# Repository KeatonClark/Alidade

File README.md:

# Alidade
A split wireless, ergo mechanical keyboard based on the switch layout of the [Corne V4](https://github.com/foostan/crkbd) by *foostan*.

View the documentation [here](https://KeatonClark.github.io/alidade)

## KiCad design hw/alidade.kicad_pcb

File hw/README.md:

# Alidade Hardware

Attribution to foostan for the board outline, switch placement, and various footprints and 3D models

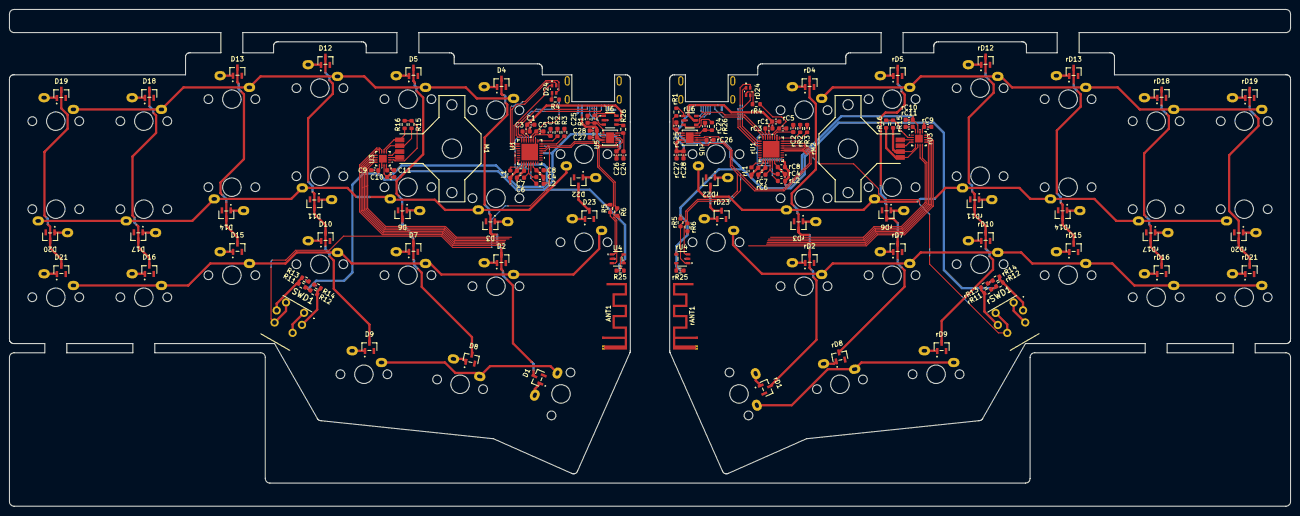
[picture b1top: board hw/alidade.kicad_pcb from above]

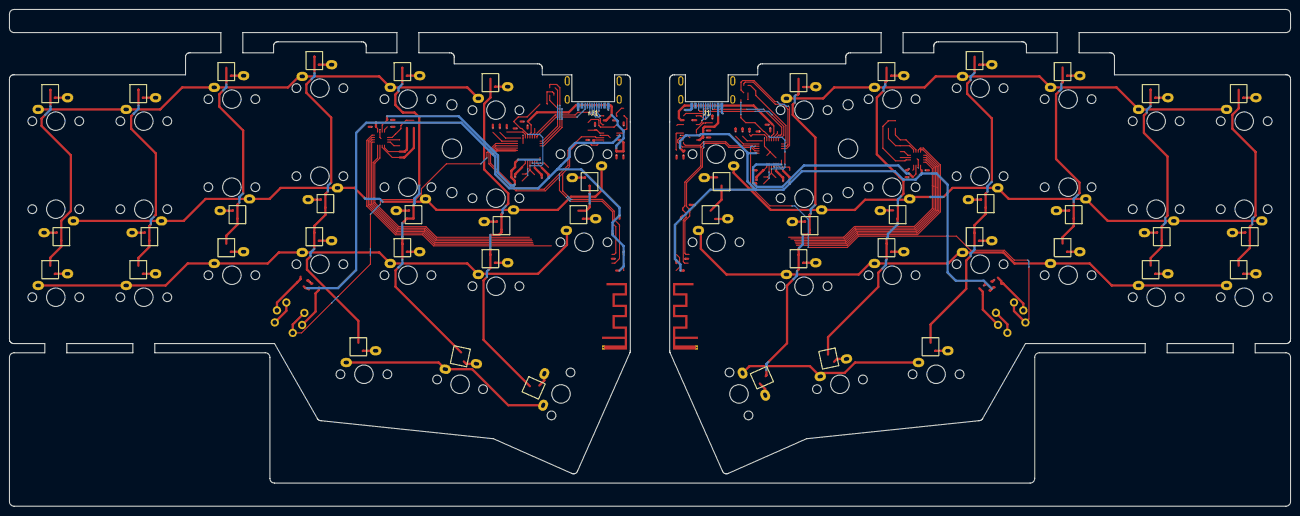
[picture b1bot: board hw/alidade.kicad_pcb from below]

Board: 4 copper layers, 277.2 x 107.5 mm, 176 parts (48 on the bottom side), 138 nets.

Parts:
ANT1: SWRA117D; Texas_SWRA117D_2.4GHz_Left
C1, C3: 1u; C_0603_1608Metric
C2: 2.2u; C_0603_1608Metric
C4, C5, C6, C7, C8: 10u; C_0603_1608Metric
C9, C10, C11, C26, C28: 100n; C_0603_1608Metric
C24, C25: 47p; C_0603_1608Metric
C27: 4.7u; C_0603_1608Metric
D1, D2, D3, D4, D5, D6, D7, D8, D9, D10, D11, D12, D13, D14, D15, D16, D17, D18, D19, D20, D21, D22, D23: BAT54; SOT23
D24: 19-237/R6GHBHC-A01/2T; 19-237_R6GHBHC-A01_2T
EXSW1, EXSW2: SW_Push; CherryMX_1u
J1: TYPE-C-31-M-13C
L1, L2: 2.2u; L_0603_1608Metric
M1: SK8701-01-005-SENSOR; SK8707-01-005-SENSOR
R1, R26: 27; R_0603_1608Metric
R2: 47k; R_0603_1608Metric
R3, R4, R13, R14: 0; R_0603_1608Metric
R5, R6, R11, R12, R25: 10k; R_0603_1608Metric
R15, R16: 2.4k; R_0603_1608Metric
SW1, SW2, SW3, SW4, SW5, SW6, SW7, SW8, SW9, SW10, SW11, SW12, SW13, SW14, SW15, SW16, SW17, SW18, SW19, SW20, SW21: SW_Push; CherryMX_1u
SWD1: 228ADS2AAWFCMBA; 228ADS2
U1: NPM1300-QEAA-R; QFN32_5X5
U3: ADS122S14IRTER; WQFN16_3X3
U4: AT24C32E-STUM-T; TSOT5_MC_MCH
U5: FT200XD; DFN-10_FTD
U6: USBLC6-2SC6; SOT23-6L_STM
rANT1: SWRA117D; Texas_SWRA117D_2.4GHz_Right
rC1, rC3: 1u; C_0603_1608Metric
rC2: 2.2u; C_0603_1608Metric
rC4, rC5, rC6, rC7, rC8: 10u; C_0603_1608Metric
rC9, rC10, rC11, rC26, rC28: 100n; C_0603_1608Metric
rC24, rC25: 47p; C_0603_1608Metric
rC27: 4.7u; C_0603_1608Metric
rD1, rD2, rD3, rD4, rD5, rD6, rD7, rD8, rD9, rD10, rD11, rD12, rD13, rD14, rD15, rD16, rD17, rD18, rD19, rD20, rD21, rD22, rD23: BAT54; SOT23
rD24: 19-237/R6GHBHC-A01/2T; 19-237_R6GHBHC-A01_2T
rEXSW1, rEXSW2: SW_Push; CherryMX_1u
rJ1: TYPE-C-31-M-13C
rL1, rL2: 2.2u; L_0603_1608Metric
rM2: SK8701-01-005-SENSOR; SK8707-01-005-SENSOR
rR1, rR26: 27; R_0603_1608Metric
rR2: 47k; R_0603_1608Metric
rR3, rR4, rR13, rR14: 0; R_0603_1608Metric
rR5, rR6, rR11, rR12, rR25: 10k; R_0603_1608Metric
rR15, rR16: 2.4k; R_0603_1608Metric
rSW1, rSW2, rSW3, rSW4, rSW5, rSW6, rSW7, rSW8, rSW9, rSW10, rSW11, rSW12, rSW13, rSW14, rSW15, rSW16, rSW17, rSW18, rSW19, rSW20, rSW21: SW_Push; CherryMX_1u
rSWD1: 228ADS2AAWFCMBA; 228ADS2
rU1: NPM1300-QEAA-R; QFN32_5X5
rU3: ADS122S14IRTER; WQFN16_3X3
rU4: AT24C32E-STUM-T; TSOT5_MC_MCH
rU5: FT200XD; DFN-10_FTD
rU6: USBLC6-2SC6; SOT23-6L_STM

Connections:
/HID/AIN0: M1.B, U3.4 (AIN3)
/HID/AIN1: M1.A, U3.3 (AIN2)
/HID/COL1: D22.3 (K), D23.3 (K)
/HID/COL2: D1.3 (K), D2.3 (K), D3.3 (K), D4.3 (K)
/HID/COL3: D5.3 (K), D6.3 (K), D7.3 (K), D8.3 (K)
/HID/COL4: D9.3 (K), D10.3 (K), D11.3 (K), D12.3 (K)
/HID/COL5: D13.3 (K), D14.3 (K), D15.3 (K)
/HID/COL6: D16.3 (K), D17.3 (K), D18.3 (K)
/HID/COL7: D19.3 (K), D20.3 (K), D21.3 (K)
/HID/REFN: M1.D, R16.2, U3.6 (AIN5/REFN/GPIO1)
/HID/REFP: M1.C, R15.1, U3.5 (AIN4/REFP/GPIO0)
/HID/ROW1: SW4.1, SW5.1, SW12.1, SW13.1, SW18.1, SW19.1
/HID/ROW2: EXSW1.1, SW3.1, SW6.1, SW11.1, SW14.1, SW17.1, SW20.1
/HID/ROW3: EXSW2.1, SW2.1, SW7.1, SW10.1, SW15.1, SW16.1, SW21.1
/HID/ROW4: SW1.1, SW8.1, SW9.1
/HID/SHPHLD: SWD1.3, SWD1.4, U1.15 (SHPHLD)
/HID/rAIN0: rM2.B, rU3.4 (AIN3)
/HID/rAIN1: rM2.A, rU3.3 (AIN2)
/HID/rCOL1: rD22.3 (K), rD23.3 (K)
/HID/rCOL2: rD1.3 (K), rD2.3 (K), rD3.3 (K), rD4.3 (K)
/HID/rCOL3: rD5.3 (K), rD6.3 (K), rD7.3 (K), rD8.3 (K)
/HID/rCOL4: rD9.3 (K), rD10.3 (K), rD11.3 (K), rD12.3 (K)
/HID/rCOL5: rD13.3 (K), rD14.3 (K), rD15.3 (K)
/HID/rCOL6: rD16.3 (K), rD17.3 (K), rD18.3 (K)
/HID/rCOL7: rD19.3 (K), rD20.3 (K), rD21.3 (K)
/HID/rREFN: rM2.D, rR16.2, rU3.6 (AIN5/REFN/GPIO1)
/HID/rREFP: rM2.C, rR15.1, rU3.5 (AIN4/REFP/GPIO0)
/HID/rROW1: rSW4.1, rSW5.1, rSW12.1, rSW13.1, rSW18.1, rSW19.1
/HID/rROW2: rEXSW1.1, rSW3.1, rSW6.1, rSW11.1, rSW14.1, rSW17.1, rSW20.1
/HID/rROW3: rEXSW2.1, rSW2.1, rSW7.1, rSW10.1, rSW15.1, rSW16.1, rSW21.1
/HID/rROW4: rSW1.1, rSW8.1, rSW9.1
/HID/rSHPHLD: rSWD1.3, rSWD1.4, rU1.15 (SHPHLD)
/MCU/SCL: R5.2, U1.14 (SCL), U4.1 (SCL), U5.6 (SCL)
/MCU/SDA: R6.2, U1.13 (SDA), U4.3 (SDA), U5.8 (SDA)
/MCU/rSCL: rR5.2, rU1.14 (SCL), rU4.1 (SCL), rU5.6 (SCL)
/MCU/rSDA: rR6.2, rU1.13 (SDA), rU4.3 (SDA), rU5.8 (SDA)
/PMIC/VBUS: C1.2, C27.1, C28.1, J1.A4 (VBUS), J1.A9 (VBUS), J1.B4 (VBUS), J1.B9 (VBUS), U1.21 (VBUS), U5.4 (VCC), U6.5 (VBUS)
/PMIC/VSYS: C4.1, C5.1, C6.1, R4.2, U1.4 (PVDD), U1.20 (VSYS)
/PMIC/rVBUS: rC1.2, rC27.1, rC28.1, rJ1.A4 (VBUS), rJ1.A9 (VBUS), rJ1.B4 (VBUS), rJ1.B9 (VBUS), rU1.21 (VBUS), rU5.4 (VCC), rU6.5 (VBUS)
/PMIC/rVSYS: rC4.1, rC5.1, rC6.1, rR4.2, rU1.4 (PVDD), rU1.20 (VSYS)
AVDD: C8.1, C10.1, L2.1, U1.32 (VOUT2), U3.15 (AVDD)
DVDD: C7.1, C9.1, C26.1, L1.1, R5.1, R6.1, R11.1, R12.2, R25.1, U1.1 (VOUT1), U1.12 (VDDIO), U3.13 (DVDD), U4.4 (VCC), U5.2 (RESET#), U5.7 (VCCIO)
GND: ANT1.2 (GND), C1.1, C2.2, C3.2, C4.2, C5.2, C6.2, C7.2, C8.2, C9.2, C10.2, C11.2, C24.2, C25.2, C26.2, C27.2, C28.2, J1.A1 (GND), J1.A12 (GND), J1.B1 (GND), J1.B12 (GND), J1.S1 (SHIELD), R2.1, R3.1, R13.2, R14.1, SWD1.1, SWD1.2, U1.2 (PVSS1), U1.6 (PVSS2), U1.18 (NTC), U1.33 (AVSS), U3.14 (GND), U3.17 (TP), U4.2 (GND), U5.9 (GND), U5.11 (GND), U6.2 (GND)
unnamed: D1.1 (A), SW1.2
unnamed: D2.1 (A), SW2.2
unnamed: D3.1 (A), SW3.2
unnamed: D4.1 (A), SW4.2
unnamed: D5.1 (A), SW5.2
unnamed: D6.1 (A), SW6.2
unnamed: D7.1 (A), SW7.2
unnamed: D8.1 (A), SW8.2
unnamed: D9.1 (A), SW9.2
unnamed: D10.1 (A), SW10.2
unnamed: D11.1 (A), SW11.2
unnamed: D12.1 (A), SW12.2
unnamed: D13.1 (A), SW13.2
unnamed: D14.1 (A), SW14.2
unnamed: D15.1 (A), SW15.2
unnamed: D16.1 (A), SW16.2
unnamed: D17.1 (A), SW17.2
unnamed: D18.1 (A), SW18.2
unnamed: D19.1 (A), SW19.2
unnamed: D20.1 (A), SW20.2
unnamed: D21.1 (A), SW21.2
unnamed: D22.1 (A), EXSW1.2
unnamed: D23.1 (A), EXSW2.2
unnamed: D24.3 (B), U1.27 (LED2)
unnamed: D24.2 (G), U1.26 (LED1)
unnamed: D24.4, R4.1
unnamed: D24.1 (R), U1.25 (LED0)
unnamed: J1.A5 (CC1), U1.23 (CC1)
unnamed: J1.B5 (CC2), U1.24 (CC2)
unnamed: J1.A6 (D+), J1.B6 (D+), U6.3 (I/O2)
unnamed: J1.A7 (D-), J1.B7 (D-), U6.1 (I/O1)
unnamed: C2.1, U1.19 (VBAT)
unnamed: R1.1, U6.6 (I/O1)
unnamed: R11.2, R13.1, SWD1.L1
unnamed: R12.1, R14.2, SWD1.L2
unnamed: R26.1, U6.4 (I/O2)
unnamed: C3.1, U1.22 (VBUSOUT)
unnamed: L1.2, U1.3 (SW1)
unnamed: R2.2, U1.17 (VSET1)
unnamed: L2.2, U1.5 (SW2)
unnamed: R3.2, U1.16 (VSET2)
unnamed: R25.2, U4.5 (WP)
unnamed: R15.2, R16.1, U3.2 (AIN1)
unnamed: C11.1, U3.16 (REFOUT)
unnamed: C25.1, R1.2, U5.1 (USBDM)
unnamed: C24.1, R26.2, U5.10 (USBDP)
unnamed: rD1.1 (A), rSW1.2
unnamed: rD2.1 (A), rSW2.2
unnamed: rD3.1 (A), rSW3.2
unnamed: rD4.1 (A), rSW4.2
unnamed: rD5.1 (A), rSW5.2
unnamed: rD6.1 (A), rSW6.2
unnamed: rD7.1 (A), rSW7.2
unnamed: rD8.1 (A), rSW8.2
unnamed: rD9.1 (A), rSW9.2
unnamed: rD10.1 (A), rSW10.2
unnamed: rD11.1 (A), rSW11.2
unnamed: rD12.1 (A), rSW12.2
unnamed: rD13.1 (A), rSW13.2
unnamed: rD14.1 (A), rSW14.2
unnamed: rD15.1 (A), rSW15.2
unnamed: rD16.1 (A), rSW16.2
unnamed: rD17.1 (A), rSW17.2
unnamed: rD18.1 (A), rSW18.2
unnamed: rD19.1 (A), rSW19.2
unnamed: rD20.1 (A), rSW20.2
unnamed: rD21.1 (A), rSW21.2
unnamed: rD22.1 (A), rEXSW1.2
unnamed: rD23.1 (A), rEXSW2.2
unnamed: rD24.3 (B), rU1.27 (LED2)
unnamed: rD24.2 (G), rU1.26 (LED1)
unnamed: rD24.4, rR4.1
unnamed: rD24.1 (R), rU1.25 (LED0)
unnamed: rJ1.A5 (CC1), rU1.23 (CC1)
unnamed: rJ1.B5 (CC2), rU1.24 (CC2)
unnamed: rJ1.A6 (D+), rJ1.B6 (D+), rU6.4 (I/O2)
unnamed: rJ1.A7 (D-), rJ1.B7 (D-), rU6.6 (I/O1)
unnamed: rC2.1, rU1.19 (VBAT)
unnamed: rR1.1, rU6.1 (I/O1)
unnamed: rR11.2, rR13.1, rSWD1.L1
unnamed: rR12.2, rR14.1, rSWD1.L2
unnamed: rR26.1, rU6.3 (I/O2)
unnamed: rC3.1, rU1.22 (VBUSOUT)
unnamed: rL1.2, rU1.3 (SW1)
unnamed: rR2.2, rU1.17 (VSET1)
unnamed: rL2.2, rU1.5 (SW2)
unnamed: rR3.2, rU1.16 (VSET2)
unnamed: rR25.2, rU4.5 (WP)
unnamed: rR15.2, rR16.1, rU3.2 (AIN1)
unnamed: rC11.1, rU3.16 (REFOUT)
unnamed: rC25.1, rR1.2, rU5.1 (USBDM)
unnamed: rC24.1, rR26.2, rU5.10 (USBDP)
rAVDD: rC8.1, rC10.1, rL2.1, rU1.32 (VOUT2), rU3.15 (AVDD)
rDVDD: rC7.1, rC9.1, rC26.1, rL1.1, rR5.1, rR6.1, rR11.1, rR12.1, rR25.1, rU1.1 (VOUT1), rU1.12 (VDDIO), rU3.13 (DVDD), rU4.4 (VCC), rU5.2 (RESET#), rU5.7 (VCCIO)
rGND: rANT1.2 (GND), rC1.1, rC2.2, rC3.2, rC4.2, rC5.2, rC6.2, rC7.2, rC8.2, rC9.2, rC10.2, rC11.2, rC24.2, rC25.2, rC26.2, rC27.2, rC28.2, rJ1.A1 (GND), rJ1.A12 (GND), rJ1.B1 (GND), rJ1.B12 (GND), rJ1.S1 (SHIELD), rR2.1, rR3.1, rR13.2, rR14.2, rSWD1.1, rSWD1.2, rU1.2 (PVSS1), rU1.6 (PVSS2), rU1.18 (NTC), rU1.33 (AVSS), rU3.14 (GND), rU3.17 (TP), rU4.2 (GND), rU5.9 (GND), rU5.11 (GND), rU6.2 (GND)

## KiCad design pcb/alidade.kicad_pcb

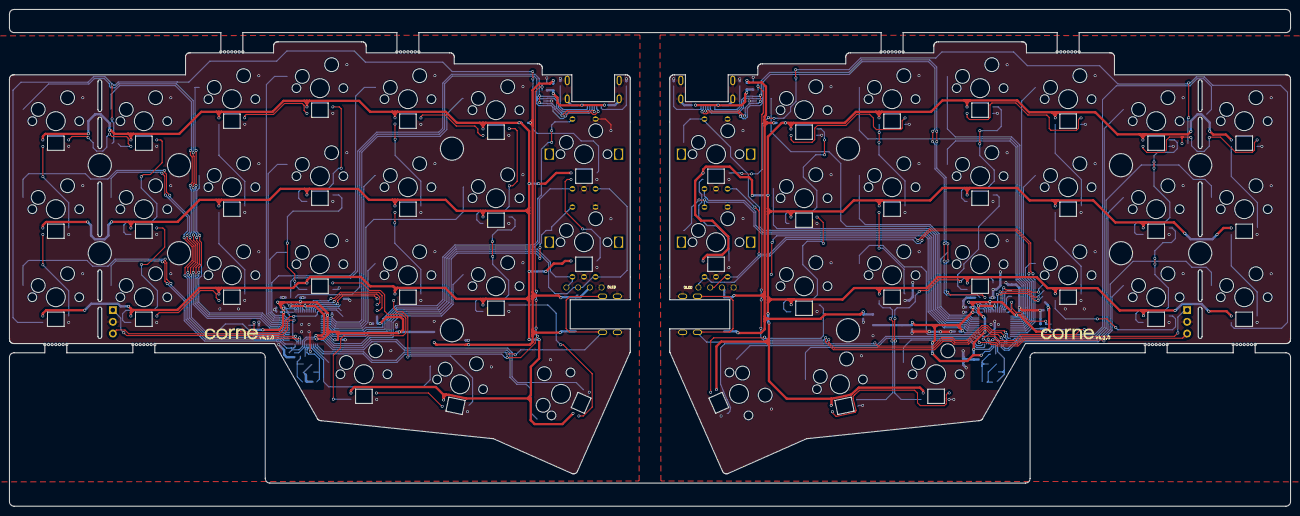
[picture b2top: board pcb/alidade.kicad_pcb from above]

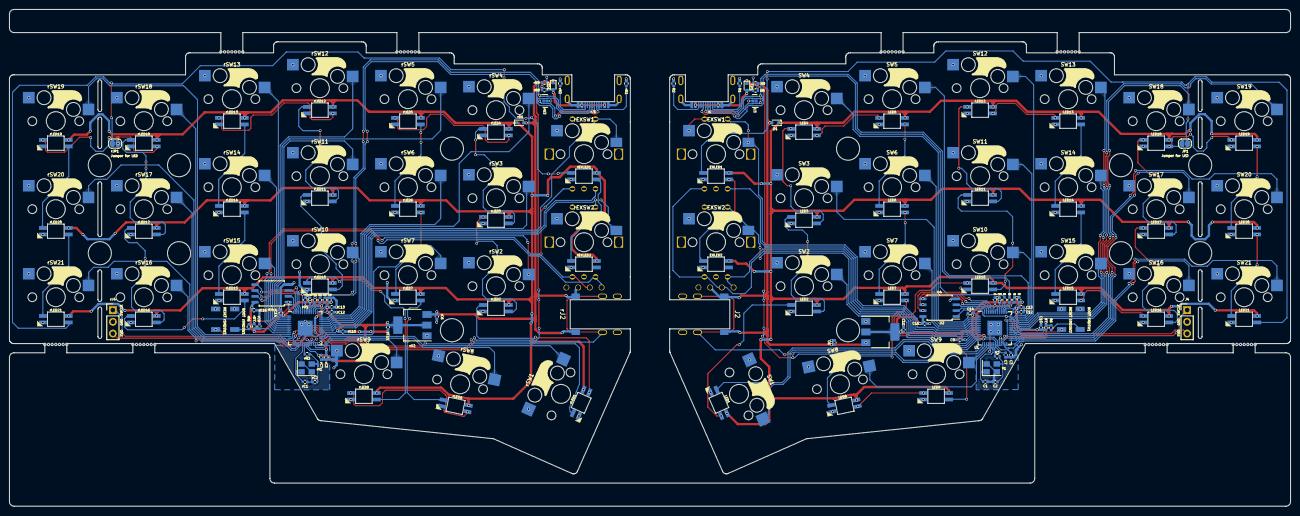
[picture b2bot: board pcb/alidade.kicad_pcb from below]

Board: 2 copper layers, 277.2 x 107.5 mm, 178 parts (168 on the bottom side), 152 nets.

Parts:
BT1, BT2, BT3, BT4: Breakaway Tabs; Breakaway_Tabs
C1, C2: 27p; C_0402_1005Metric
C3, C4, C7, C9, C10, C12, C13, C14, C15: 100n; C_0402_1005Metric
C5, C8, C16: 1u; C_0402_1005Metric
C6, C11: 10u; C_0402_1005Metric
D1: 1N4148WT; D_SOD-523
EXLED1, EXLED2: YS-SK6812MINI-E
EXSW1, EXSW2: RotaryEncoder_Switch; keyswitch_cherrymx_hotswap_1u_rotary_encoder_ec12
J1: TYPE-C-31-M-13C
J2: TRS; PJ-398A-5A_PJ-399B-6A
J3: Conn_01x04; OLED
J4: Conn_01x03; PinHeader_1x03_P2.54mm_Vertical
JP1: SolderJumper_2_Bridged; SolderJumper-2_P1.3mm_Open_RoundedPad1.0x1.5mm
LED1, LED2, LED3, LED4, LED5, LED6, LED7, LED8, LED9, LED10, LED11, LED12, LED13, LED14, LED15, LED16, LED17, LED18, LED19, LED20, LED21: YS-SK6812MINI-E
R1, R2: 5.1k; R_0402_1005Metric
R3, R6: 1k; R_0402_1005Metric
R4, R5: 27; R_0402_1005Metric
R7: 10k; R_0402_1005Metric
R8: 5.6k; R_0402_1005Metric
R9: 10K; R_0402_1005Metric
SMDSW1, SMDSW2: TS-1088R-02026
SW1: SW_Push; keyswitch_cherrymx_hotswap_1.5u
SW2, SW3, SW4, SW5, SW6, SW7, SW8, SW9, SW10, SW11, SW12, SW13, SW14, SW15, SW16, SW17, SW18, SW19, SW20, SW21: SW_Push; keyswitch_cherrymx_hotswap_1u
U1: RP2040; QFN-56-1EP_7x7mm_P0.4mm_EP3.2x3.2mm
U2: NCP1117LPST33T3G; SOT-223-3_TabPin2
U3: TPD4E05U06DQAR; USON-10_2.5x1.0mm_P0.5mm
U4: W25Q128JVSIQ; SOIC-8_5.23x5.23mm_P1.27mm
Y1: 12MHz 18pF; Crystal_SMD_3225-4Pin_3.2x2.5mm
ZD1: RB521S30T1G; D_SOD-523
rBT1, rBT2, rBT3, rBT4: Breakaway Tabs; Breakaway_Tabs
rC1, rC2: 27p; C_0402_1005Metric
rC3, rC4, rC7, rC9, rC10, rC12, rC13, rC14, rC15: 100n; C_0402_1005Metric
rC5, rC8, rC16: 1u; C_0402_1005Metric
rC6, rC11: 10u; C_0402_1005Metric
rD1: 1N4148WT; D_SOD-523
rEXLED1, rEXLED2: YS-SK6812MINI-E
rEXSW1, rEXSW2: RotaryEncoder_Switch; keyswitch_cherrymx_hotswap_1u_rotary_encoder_ec12
rJ1: TYPE-C-31-M-13C
rJ2: TRS; PJ-398A-5A_PJ-399B-6A
rJ3: Conn_01x04; OLED
rJ4: Conn_01x03; PinHeader_1x03_P2.54mm_Vertical
rJP1: SolderJumper_2_Bridged; SolderJumper-2_P1.3mm_Open_RoundedPad1.0x1.5mm
rLED1, rLED2, rLED3, rLED4, rLED5, rLED6, rLED7, rLED8, rLED9, rLED10, rLED11, rLED12, rLED13, rLED14, rLED15, rLED16, rLED17, rLED18, rLED19, rLED20, rLED21: YS-SK6812MINI-E
rR1, rR2: 5.1k; R_0402_1005Metric
rR3, rR6: 1k; R_0402_1005Metric
rR4, rR5: 27; R_0402_1005Metric
rR7: 10k; R_0402_1005Metric
rR8: 5.6k; R_0402_1005Metric
rR9: 10K; R_0402_1005Metric
rSMDSW1, rSMDSW2: TS-1088R-02026
rSW1: SW_Push; keyswitch_cherrymx_hotswap_1.5u
rSW2, rSW3, rSW4, rSW5, rSW6, rSW7, rSW8, rSW9, rSW10, rSW11, rSW12, rSW13, rSW14, rSW15, rSW16, rSW17, rSW18, rSW19, rSW20, rSW21: SW_Push; keyswitch_cherrymx_hotswap_1u
rU1: RP2040; QFN-56-1EP_7x7mm_P0.4mm_EP3.2x3.2mm
rU2: NCP1117LPST33T3G; SOT-223-3_TabPin2
rU3: TPD4E05U06DQAR; USON-10_2.5x1.0mm_P0.5mm
rU4: W25Q128JVSIQ; SOIC-8_5.23x5.23mm_P1.27mm
rY1: 12MHz 18pF; Crystal_SMD_3225-4Pin_3.2x2.5mm
rZD1: RB521S30T1G; D_SOD-523

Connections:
+1V1: C3.1, C4.1, C5.1, U1.23 (DVDD), U1.45 (VREG_VOUT), U1.50 (DVDD)
+1V1R: rC3.1, rC4.1, rC5.1, rU1.23 (DVDD), rU1.45 (VREG_VOUT), rU1.50 (DVDD)
+3V3: C7.1, C8.1, C9.1, C10.1, C11.1, C12.1, C13.1, C14.1, C15.1, C16.1, R7.2, U1.1 (IOVDD), U1.10 (IOVDD), U1.22 (IOVDD), U1.32 (GPIO21), U1.33 (IOVDD), U1.42 (IOVDD), U1.43 (ADC_AVDD), U1.44 (VREG_IN), U1.48 (USB_VDD), U1.49 (IOVDD), U2.2 (VO), U4.8 (VCC)
+3V3R: rC7.1, rC8.1, rC9.1, rC10.1, rC11.1, rC12.1, rC13.1, rC14.1, rC15.1, rC16.1, rR7.2, rU1.1 (IOVDD), rU1.10 (IOVDD), rU1.22 (IOVDD), rU1.33 (IOVDD), rU1.42 (IOVDD), rU1.43 (ADC_AVDD), rU1.44 (VREG_IN), rU1.48 (USB_VDD), rU1.49 (IOVDD), rU2.2 (VO), rU4.8 (VCC)
+5V: C6.1, D1.2 (A), J2.T, J3.3, U2.3 (VI), ZD1.1 (K)
+5VR: rC6.1, rD1.2 (A), rJ2.T, rJ3.3, rU2.3 (VI), rZD1.1 (K)
/left/D+: J1.A6 (D+), J1.B6 (D+), R4.1, U3.1 (D1+), U3.4 (D2+), U3.7 (NC), U3.10 (NC)
/left/D-: J1.A7 (D-), J1.B7 (D-), R5.2, U3.2 (D1-), U3.5 (D2-), U3.6 (NC), U3.9 (NC)
/left/KEY1: SW1.1, U1.14 (GPIO11)
/left/KEY2: SW2.1, U1.12 (GPIO9)
/left/KEY3: SW3.1, U1.4 (GPIO2)
/left/KEY4: SW4.1, U1.2 (GPIO0)
/left/KEY5: SW5.1, U1.41 (GPIO29_ADC3)
/left/KEY6: SW6.1, U1.3 (GPIO1)
/left/KEY7: SW7.1, U1.5 (GPIO3)
/left/KEY8: SW8.1, U1.18 (GPIO15)
/left/KEY9: SW9.1, U1.17 (GPIO14)
/left/KEY10: SW10.1, U1.40 (GPIO28_ADC2)
/left/KEY11: SW11.1, U1.39 (GPIO27_ADC1)
/left/KEY12: SW12.1, U1.38 (GPIO26_ADC0)
/left/KEY13: SW13.1, U1.35 (GPIO23)
/left/KEY14: SW14.1, U1.36 (GPIO24)
/left/KEY15: SW15.1, U1.37 (GPIO25)
/left/KEY16: SW16.1, U1.27 (GPIO16)
/left/KEY17: SW17.1, U1.29 (GPIO18)
/left/KEY18: SW18.1, U1.31 (GPIO20)
/left/KEY19: SW19.1, U1.34 (GPIO22)
/left/KEY20: SW20.1, U1.30 (GPIO19)
/left/KEY21: SW21.1, U1.28 (GPIO17)
/left/KEYEX1: EXSW1.S2, U1.6 (GPIO4)
/left/KEYEX2: EXSW2.S2, U1.11 (GPIO8)
/left/LED: LED1.4 (DIN), U1.13 (GPIO10)
/left/QSPI_SCLK: U1.52 (QSPI_SCLK), U4.6 (CLK)
/left/QSPI_SD0: U1.53 (QSPI_SD0), U4.5 (DI(IO0))
/left/QSPI_SD1: U1.55 (QSPI_SD1), U4.2 (DO(IO1))
/left/QSPI_SD2: U1.54 (QSPI_SD2), U4.3 (IO2)
/left/QSPI_SD3: U1.51 (QSPI_SD3), U4.7 (IO3)
/left/QSPI_SS: R6.1, R7.1, U1.56 (QSPI_SS), U4.1 (~CS)
/left/RE0A: EXSW1.A, U1.7 (GPIO5)
/left/RE1A: EXSW2.A, J3.1, U1.8 (GPIO6)
/left/REB: EXSW1.B, EXSW2.B, J3.2, U1.9 (GPIO7)
/left/SWCLK: J4.1, U1.24 (SWCLK)
/left/SWD: J4.3, U1.25 (SWD)
/left/TX: J2.R, U1.15 (GPIO12)
/left/USB_VBUS_PIN: R8.2, R9.1, U1.16 (GPIO13)
/right/D+: rJ1.A6 (D+), rJ1.B6 (D+), rR4.1, rU3.1 (D1+), rU3.4 (D2+), rU3.7 (NC), rU3.10 (NC)
/right/D-: rJ1.A7 (D-), rJ1.B7 (D-), rR5.2, rU3.2 (D1-), rU3.5 (D2-), rU3.6 (NC), rU3.9 (NC)
/right/KEY1: rSW1.1, rU1.30 (GPIO19)
/right/KEY2: rSW2.1, rU1.34 (GPIO22)
/right/KEY3: rSW3.1, rU1.38 (GPIO26_ADC0)
/right/KEY4: rSW4.1, rU1.39 (GPIO27_ADC1)
/right/KEY5: rSW5.1, rU1.3 (GPIO1)
/right/KEY6: rSW6.1, rU1.40 (GPIO28_ADC2)
/right/KEY7: rSW7.1, rU1.31 (GPIO20)
/right/KEY8: rSW8.1, rU1.28 (GPIO17)
/right/KEY9: rSW9.1, rU1.27 (GPIO16)
/right/KEY10: rSW10.1, rU1.41 (GPIO29_ADC3)
/right/KEY11: rSW11.1, rU1.2 (GPIO0)
/right/KEY12: rSW12.1, rU1.4 (GPIO2)
/right/KEY13: rSW13.1, rU1.5 (GPIO3)
/right/KEY14: rSW14.1, rU1.6 (GPIO4)
/right/KEY15: rSW15.1, rU1.7 (GPIO5)
/right/KEY16: rSW16.1, rU1.29 (GPIO18)
/right/KEY17: rSW17.1, rU1.17 (GPIO14)
/right/KEY18: rSW18.1, rU1.12 (GPIO9)
/right/KEY19: rSW19.1, rU1.11 (GPIO8)
/right/KEY20: rSW20.1, rU1.14 (GPIO11)
/right/KEY21: rSW21.1, rU1.18 (GPIO15)
/right/KEYEX1: rEXSW1.S2, rU1.37 (GPIO25)
/right/KEYEX2: rEXSW2.S2, rU1.35 (GPIO23)
/right/LED: rLED1.4 (DIN), rU1.13 (GPIO10)
/right/QSPI_SCLK: rU1.52 (QSPI_SCLK), rU4.6 (CLK)
/right/QSPI_SD0: rU1.53 (QSPI_SD0), rU4.5 (DI(IO0))
/right/QSPI_SD1: rU1.55 (QSPI_SD1), rU4.2 (DO(IO1))
/right/QSPI_SD2: rU1.54 (QSPI_SD2), rU4.3 (IO2)
/right/QSPI_SD3: rU1.51 (QSPI_SD3), rU4.7 (IO3)
/right/QSPI_SS: rR6.1, rR7.1, rU1.56 (QSPI_SS), rU4.1 (~CS)
/right/RE0A: rEXSW1.A, rU1.36 (GPIO24)
/right/RE1A: rEXSW2.A, rJ3.1, rU1.8 (GPIO6)
/right/REB: rEXSW1.B, rEXSW2.B, rJ3.2, rU1.9 (GPIO7)
/right/SWCLK: rJ4.1, rU1.24 (SWCLK)
/right/SWD: rJ4.3, rU1.25 (SWD)
/right/TX: rJ2.R, rU1.15 (GPIO12)
/right/USB_VBUS_PIN: rR8.2, rR9.1, rU1.16 (GPIO13)
GND: C1.2, C2.2, C3.2, C4.2, C5.2, C6.2, C7.2, C8.2, C9.2, C10.2, C11.2, C12.2, C13.2, C14.2, C15.2, C16.2, EXLED1.3 (VSS), EXLED2.3 (VSS), EXSW1.C, EXSW1.S1, EXSW2.C, EXSW2.S1, J1.A1 (GND), J1.A12 (GND), J1.B1 (GND), J1.B12 (GND), J1.S1 (SHIELD), J2.S, J3.4, J4.2, LED1.3 (VSS), LED2.3 (VSS), LED3.3 (VSS), LED4.3 (VSS), LED5.3 (VSS), LED6.3 (VSS), LED7.3 (VSS), LED8.3 (VSS), LED9.3 (VSS), LED10.3 (VSS), LED11.3 (VSS), LED12.3 (VSS), LED13.3 (VSS), LED14.3 (VSS), LED15.3 (VSS), LED16.3 (VSS), LED17.3 (VSS), LED18.3 (VSS), LED19.3 (VSS), LED20.3 (VSS), LED21.3 (VSS), R1.1, R2.1, R9.2, SMDSW1.1, SMDSW2.1, SW1.2, SW2.2, SW3.2, SW4.2, SW5.2, SW6.2, SW7.2, SW8.2, SW9.2, SW10.2, SW11.2, SW12.2, SW13.2, SW14.2, SW15.2, SW16.2, SW17.2, SW18.2, SW19.2, SW20.2, SW21.2, U1.19 (TESTEN), U1.57 (GND), U2.1 (GND), U3.3 (GND), U3.8 (GND), U4.4 (GND), Y1.2, Y1.4
GNDR: rC1.2, rC2.2, rC3.2, rC4.2, rC5.2, rC6.2, rC7.2, rC8.2, rC9.2, rC10.2, rC11.2, rC12.2, rC13.2, rC14.2, rC15.2, rC16.2, rEXLED1.3 (VSS), rEXLED2.3 (VSS), rEXSW1.C, rEXSW1.S1, rEXSW2.C, rEXSW2.S1, rJ1.A1 (GND), rJ1.A12 (GND), rJ1.B1 (GND), rJ1.B12 (GND), rJ1.S1 (SHIELD), rJ2.S, rJ3.4, rJ4.2, rLED1.3 (VSS), rLED2.3 (VSS), rLED3.3 (VSS), rLED4.3 (VSS), rLED5.3 (VSS), rLED6.3 (VSS), rLED7.3 (VSS), rLED8.3 (VSS), rLED9.3 (VSS), rLED10.3 (VSS), rLED11.3 (VSS), rLED12.3 (VSS), rLED13.3 (VSS), rLED14.3 (VSS), rLED15.3 (VSS), rLED16.3 (VSS), rLED17.3 (VSS), rLED18.3 (VSS), rLED19.3 (VSS), rLED20.3 (VSS), rLED21.3 (VSS), rR1.1, rR2.1, rR9.2, rSMDSW1.1, rSMDSW2.1, rSW1.2, rSW2.2, rSW3.2, rSW4.2, rSW5.2, rSW6.2, rSW7.2, rSW8.2, rSW9.2, rSW10.2, rSW11.2, rSW12.2, rSW13.2, rSW14.2, rSW15.2, rSW16.2, rSW17.2, rSW18.2, rSW19.2, rSW20.2, rSW21.2, rU1.19 (TESTEN), rU1.32 (GPIO21), rU1.57 (GND), rU2.1 (GND), rU3.3 (GND), rU3.8 (GND), rU4.4 (GND), rY1.2, rY1.4
unnamed: C2.1, R3.1, Y1.3
unnamed: D1.1 (K), EXLED1.1 (VDD), EXLED2.1 (VDD), LED1.1 (VDD), LED2.1 (VDD), LED3.1 (VDD), LED4.1 (VDD), LED5.1 (VDD), LED6.1 (VDD), LED7.1 (VDD), LED8.1 (VDD), LED9.1 (VDD), LED10.1 (VDD), LED11.1 (VDD), LED12.1 (VDD), LED13.1 (VDD), LED14.1 (VDD), LED15.1 (VDD), LED16.1 (VDD), LED17.1 (VDD), LED18.1 (VDD), LED19.1 (VDD), LED20.1 (VDD), LED21.1 (VDD)
unnamed: EXLED1.4 (DIN), JP1.2 (B), LED21.2 (DOUT)
unnamed: EXLED1.2 (DOUT), EXLED2.4 (DIN)
unnamed: J1.A5 (CC1), R1.2
unnamed: J1.B5 (CC2), R2.2
unnamed: JP1.1 (A), LED18.2 (DOUT), LED19.4 (DIN)
unnamed: LED1.2 (DOUT), LED2.4 (DIN)
unnamed: LED2.2 (DOUT), LED3.4 (DIN)
unnamed: LED3.2 (DOUT), LED4.4 (DIN)
unnamed: LED4.2 (DOUT), LED5.4 (DIN)
unnamed: LED5.2 (DOUT), LED6.4 (DIN)
unnamed: LED6.2 (DOUT), LED7.4 (DIN)
unnamed: LED7.2 (DOUT), LED8.4 (DIN)
unnamed: LED8.2 (DOUT), LED9.4 (DIN)
unnamed: LED9.2 (DOUT), LED10.4 (DIN)
unnamed: LED10.2 (DOUT), LED11.4 (DIN)
unnamed: LED11.2 (DOUT), LED12.4 (DIN)
unnamed: LED12.2 (DOUT), LED13.4 (DIN)
unnamed: LED13.2 (DOUT), LED14.4 (DIN)
unnamed: LED14.2 (DOUT), LED15.4 (DIN)
unnamed: LED15.2 (DOUT), LED16.4 (DIN)
unnamed: LED16.2 (DOUT), LED17.4 (DIN)
unnamed: LED17.2 (DOUT), LED18.4 (DIN)
unnamed: LED19.2 (DOUT), LED20.4 (DIN)
unnamed: LED20.2 (DOUT), LED21.4 (DIN)
unnamed: R6.2, SMDSW1.2
unnamed: SMDSW2.2, U1.26 (RUN)
unnamed: R5.1, U1.46 (USB_DM)
unnamed: R4.2, U1.47 (USB_DP)
unnamed: C1.1, U1.20 (XIN), Y1.1
unnamed: R3.2, U1.21 (XOUT)
unnamed: rC2.1, rR3.1, rY1.3
unnamed: rD1.1 (K), rEXLED1.1 (VDD), rEXLED2.1 (VDD), rLED1.1 (VDD), rLED2.1 (VDD), rLED3.1 (VDD), rLED4.1 (VDD), rLED5.1 (VDD), rLED6.1 (VDD), rLED7.1 (VDD), rLED8.1 (VDD), rLED9.1 (VDD), rLED10.1 (VDD), rLED11.1 (VDD), rLED12.1 (VDD), rLED13.1 (VDD), rLED14.1 (VDD), rLED15.1 (VDD), rLED16.1 (VDD), rLED17.1 (VDD), rLED18.1 (VDD), rLED19.1 (VDD), rLED20.1 (VDD), rLED21.1 (VDD)
unnamed: rEXLED1.4 (DIN), rJP1.2 (B), rLED21.2 (DOUT)
unnamed: rEXLED1.2 (DOUT), rEXLED2.4 (DIN)
unnamed: rJ1.A5 (CC1), rR1.2
unnamed: rJ1.B5 (CC2), rR2.2
unnamed: rJP1.1 (A), rLED18.2 (DOUT), rLED19.4 (DIN)
unnamed: rLED1.2 (DOUT), rLED2.4 (DIN)
unnamed: rLED2.2 (DOUT), rLED3.4 (DIN)
unnamed: rLED3.2 (DOUT), rLED4.4 (DIN)
unnamed: rLED4.2 (DOUT), rLED5.4 (DIN)
unnamed: rLED5.2 (DOUT), rLED6.4 (DIN)
unnamed: rLED6.2 (DOUT), rLED7.4 (DIN)
unnamed: rLED7.2 (DOUT), rLED8.4 (DIN)
unnamed: rLED8.2 (DOUT), rLED9.4 (DIN)
unnamed: rLED9.2 (DOUT), rLED10.4 (DIN)
unnamed: rLED10.2 (DOUT), rLED11.4 (DIN)
unnamed: rLED11.2 (DOUT), rLED12.4 (DIN)
unnamed: rLED12.2 (DOUT), rLED13.4 (DIN)
unnamed: rLED13.2 (DOUT), rLED14.4 (DIN)
unnamed: rLED14.2 (DOUT), rLED15.4 (DIN)
unnamed: rLED15.2 (DOUT), rLED16.4 (DIN)
unnamed: rLED16.2 (DOUT), rLED17.4 (DIN)
unnamed: rLED17.2 (DOUT), rLED18.4 (DIN)
unnamed: rLED19.2 (DOUT), rLED20.4 (DIN)
unnamed: rLED20.2 (DOUT), rLED21.4 (DIN)
unnamed: rR6.2, rSMDSW1.2
unnamed: rSMDSW2.2, rU1.26 (RUN)
unnamed: rR5.1, rU1.46 (USB_DM)
unnamed: rR4.2, rU1.47 (USB_DP)
unnamed: rC1.1, rU1.20 (XIN), rY1.1
unnamed: rR3.2, rU1.21 (XOUT)
VBUS: J1.A4 (VBUS), J1.A9 (VBUS), J1.B4 (VBUS), J1.B9 (VBUS), R8.1, ZD1.2 (A)
VBUSR: rJ1.A4 (VBUS), rJ1.A9 (VBUS), rJ1.B4 (VBUS), rJ1.B9 (VBUS), rR8.1, rZD1.2 (A)

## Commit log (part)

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2025-09-02 KiBot installation
2025-09-04 Initial pcb commit
2025-11-08 A bunch of kibot stuff. Some stuff is still broken. Use kibot-check
2025-11-08 KiDiff setup
2025-11-10 Add corne v4 source
2026-03-01 clean corne source, setup libraries, place main components
2026-03-03 Power schematic with npm1100 setup
2026-03-03 Add sheet pins
2026-03-03 Sheet pin directions
2026-03-04 Battery Monitor
2026-03-05 Decoupling caps
2026-03-06 Switch matrix and sheet pins
2026-03-24 Update to NPM1300 for 4 power rails (needed for fpga). NPM1300 still needs decoupling caps
2026-03-25 Sheet pins
2026-03-26 FPGA symbol
2026-03-28 Decoder symbol
2026-03-28 Place decoder and update switches
2026-03-29 Place FPGA
2026-03-29 rename file
2026-03-29 symbols for trackpoint
2026-03-29 Place and connect trackpoint module
2026-03-30 Hook up mcu
2026-03-30 Debug header
2026-03-31 remove vbusout power flag
2026-03-31 Simple kibot config
2026-03-31 hid page erc fixes
2026-03-31 mcu page erc
2026-03-31 all true erc errors solved
2026-03-31 nix build schematic and erc
2026-03-31 typo
2026-03-31 Free up storage with nothing-but-nix
2026-03-31 Use smaller kicad package
2026-04-01 Add license and organize repo
2026-04-01 Don't zip results and attributions to foostan
2026-04-02 Install License and BoM
2026-04-02 add datasheets
2026-04-02 update github action
2026-04-04 ICE40UP footprint and symbol
2026-04-04 Use ICE40UP instead of UL
2026-04-04 Remove SN74LVC138A as we now have enough pins on the UP
2026-04-04 remove datasheet
2026-04-12 SK8701-01-005 sensor footprint with diamond plate
2026-04-14 remove unused footprints. add sod-523
2026-04-14 pull ups on rows
2026-04-15 0603 footprint
2026-04-15 apply 0603 footprint
2026-04-17 add some LCSC part numbers
2026-04-19 Use bat54 instead
2026-04-19 Upstream checksum changed?
2026-05-16 Remove FPGA, no longer needed
2026-05-18 Update symbol, use ads122S for bridge measurement
2026-05-18 Update workflow
2026-05-21 Solve erc errors
